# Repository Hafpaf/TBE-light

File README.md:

# TBE light
These are the source files for TBE lights shown at MCH2022. Original wiki page can be found here: [wiki.mch2022.org](https://wiki.mch2022.org/TBE_light)

## Credits
This project was funded by the [IFCAT foundation](https://ifcat.org/) for the technology festival [MCH2022](https://mch2022.org/).

Main contributors where:
- [Hafnium](https://github.com/hafpaf/): holding everything together
- [Oliver Taubenheim](https://www.facebook.com/a2kOliverTbm): CAD modelling
- [Richard Graham](https://github.com/Richard42Graham): PCB design

A big thanks to all contributors that helped during the prototyping of this project.

## Details

The LED controller uses an ESP32 with an LAN8720A chip for Ethernet connection and is compatible with [WLED](https://github.com/Aircoookie/WLED).

The repository is split into two categories
- [PCB](./PCB/): contains Gerber files for LED controller board, as well as an component list.
-  [CAD](./CAD/): contains to Adobe Illustrator files that can be opened in [Lightburn](https://lightburnsoftware.com/) or similar laser cutting software.

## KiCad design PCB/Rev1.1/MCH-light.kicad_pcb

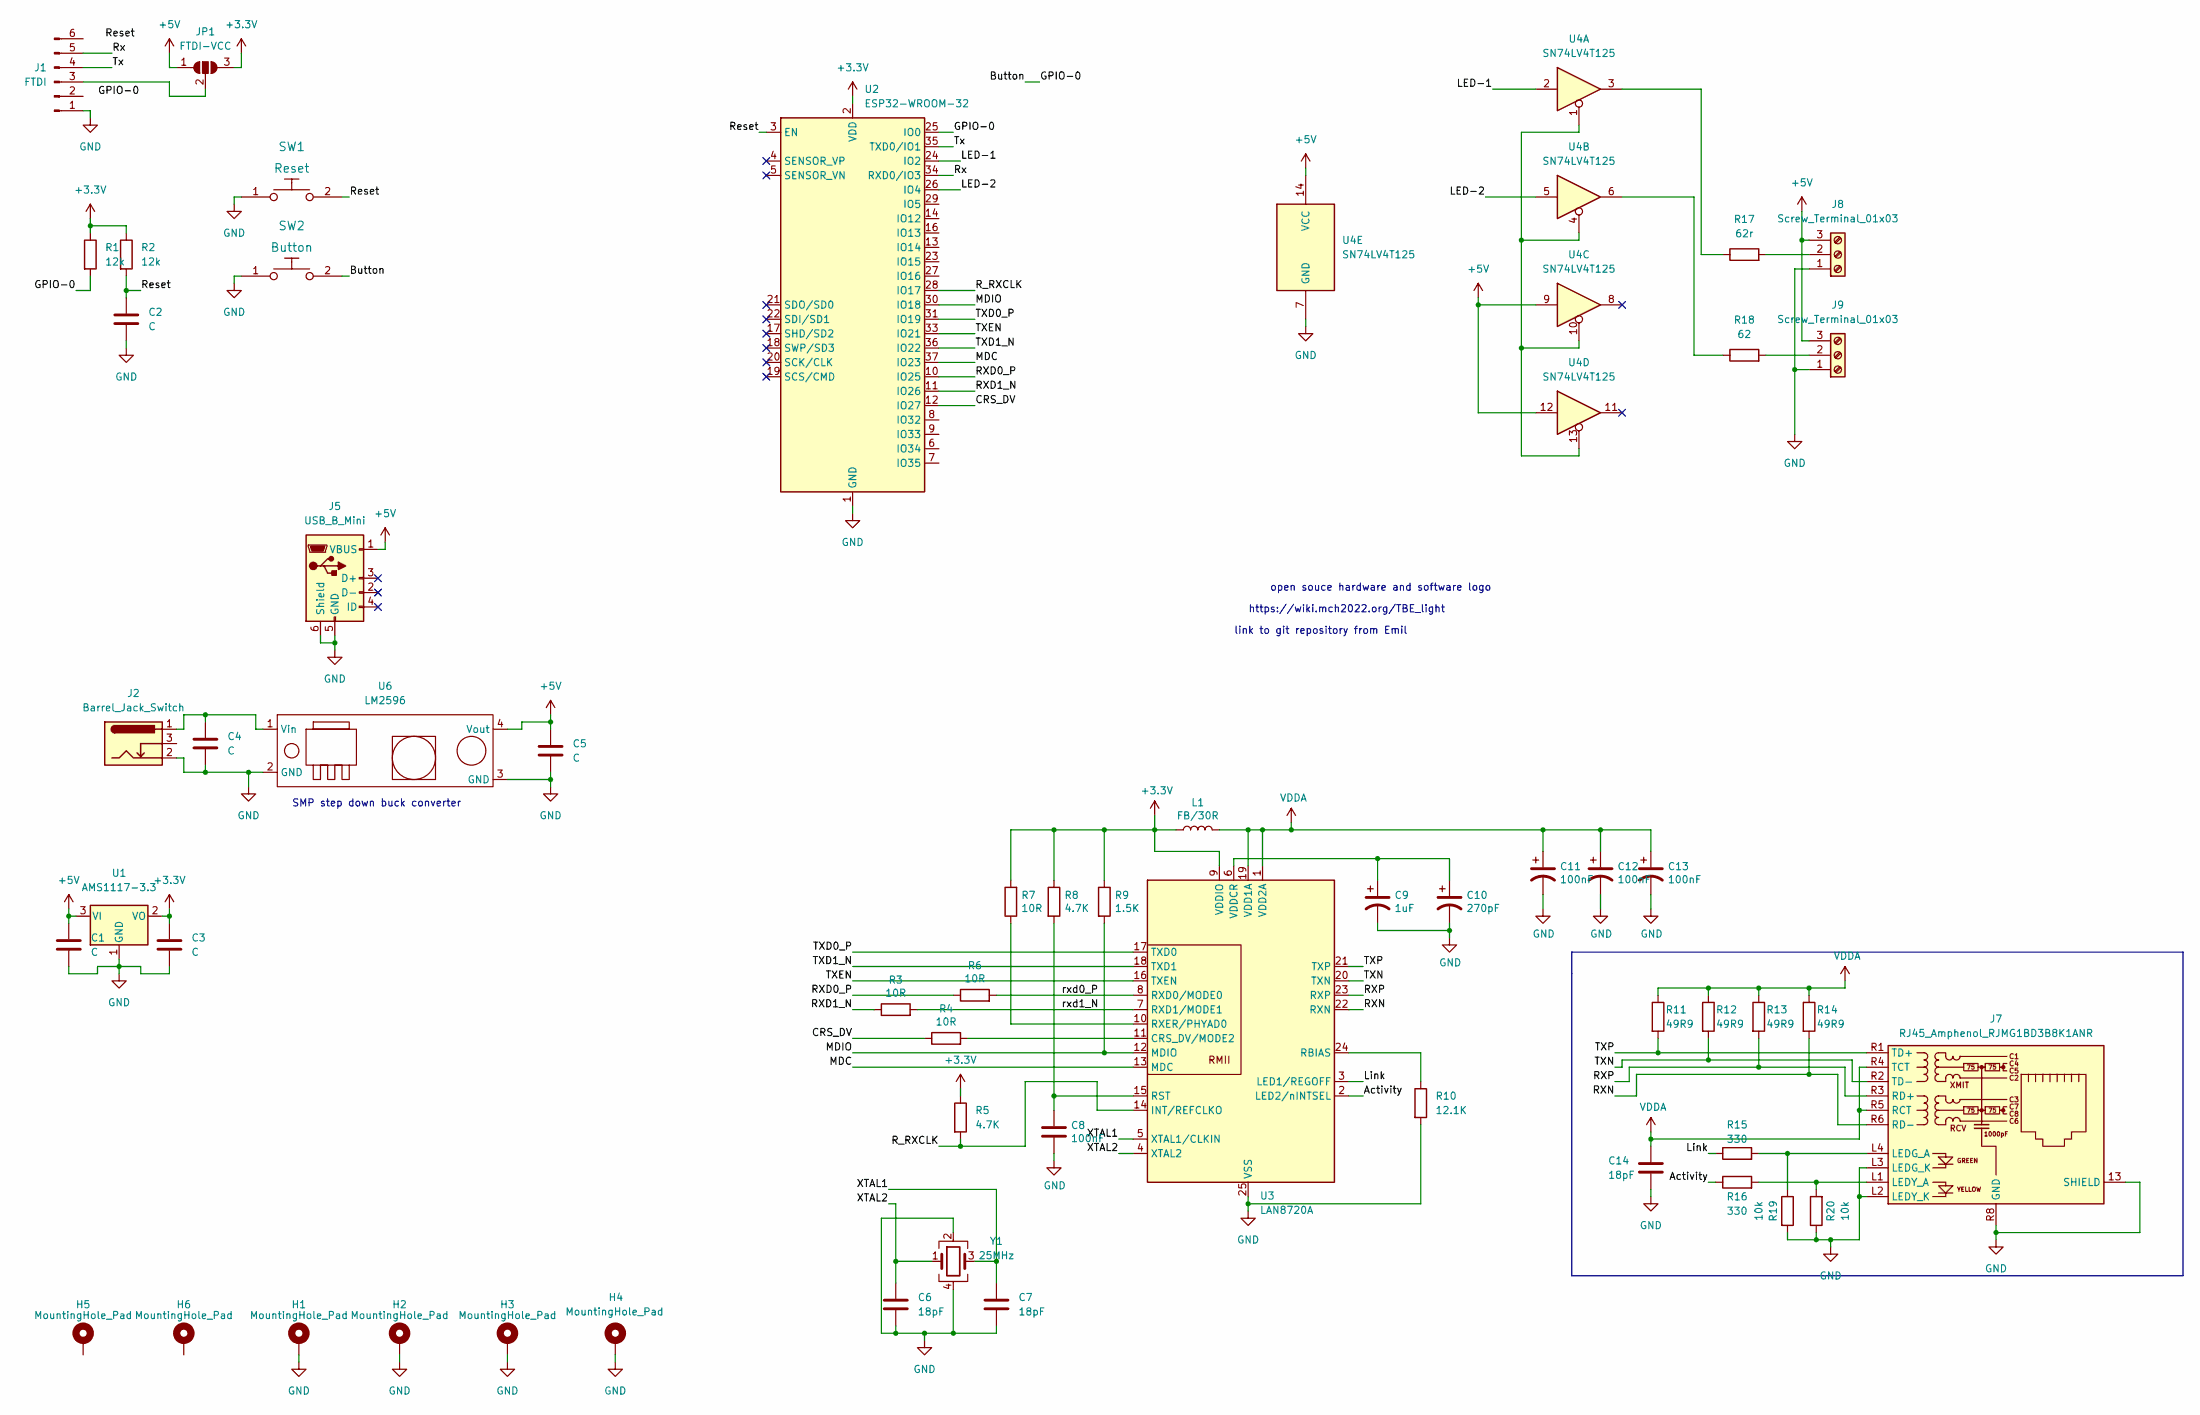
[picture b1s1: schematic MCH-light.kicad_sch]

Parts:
C1, C2, C3, C4, C5: C; C_0805_2012Metric
C6, C7, C14: 18pF; C_0805_2012Metric
C8, C11, C12, C13: 100nF; C_0603_1608Metric
C9: 1uF; C_0603_1608Metric
C10: 270pF; C_0603_1608Metric
H1, H2, H3, H4, H5, H6: MountingHole_Pad; MountingHole_3.2mm_M3_Pad
J1: FTDI; PinSocket_1x06_P2.54mm_Vertical
J2: Barrel_Jack_Switch; BarrelJack_GCT_DCJ200-10-A_Horizontal
J5: USB_B_Mini; USB_Micro-AB_Molex_47590-0001; JLC-pcb-part C136001
J7: RJ45_Amphenol_RJMG1BD3B8K1ANR; JLC-pcb-part C456388
J8, J9: Screw_Terminal_01x03; PinSocket_1x03_P2.54mm_Vertical
JP1: FTDI-VCC; SolderJumper-3_P1.3mm_Open_RoundedPad1.0x1.5mm
L1: FB/30R; L_0805_2012Metric
R1, R2: 12k; R_0603_1608Metric
R3, R4, R6, R7: 10R; R_0603_1608Metric
R5: 4.7K; C_0805_2012Metric
R8: 4.7K; R_0603_1608Metric
R9: 1.5K; R_0603_1608Metric
R10: 12.1K; R_0603_1608Metric
R11, R12, R13, R14: 49R9; R_0603_1608Metric
R15, R16: 330; R_0603_1608Metric
R17: 62r; R_0603_1608Metric
R18: 62; R_0603_1608Metric
R19, R20: 10k; R_0603_1608Metric
SW1: Reset; SW_PUSH_6mm; JLC-pcb-part C13828
SW2: Button; SW_PUSH_6mm; JLC-pcb-part C13828
U1: AMS1117-3.3; SOT-223-3_TabPin2; JLC-pcb-part C173386
U2: ESP32-WROOM-32; JLC-pcb-part C473012
U3: LAN8720A; QFN-24-1EP_4x4mm_P0.5mm_EP2.6x2.6mm; JLC-pcb-part C45223
U4: SN74LV4T125; TSSOP-14_4.4x5mm_P0.65mm; JLC-pcb-part C90755
U6: LM2596; LM2596-Module
Y1: 25MHz; Crystal_SMD_Abracon_ABM8G-4Pin_3.2x2.5mm

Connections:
+3V3: C3.1, JP1.3 (B), L1.1, R1.1, R2.1, R5.1, R7.2, R8.1, R9.1, U1.2 (VO), U2.2 (VDD), U3.9 (VDDIO)
+5V: C1.1, C5.1, J5.1 (VBUS), J8.3, J9.3, JP1.1 (A), U1.3 (VI), U4.9, U4.12, U4.14 (VCC), U6.4 (Vout)
/Activity: R16.1, U3.2 (LED2/nINTSEL)
/Button: R1.2, SW2.2, U2.25 (IO0)
/CRS_DV: R4.1, U2.12 (IO27)
/LED-1: U2.24 (IO2), U4.2
/LED-2: U2.26 (IO4), U4.5
/Link: R15.1, U3.3 (LED1/REGOFF)
/MDC: U2.37 (IO23), U3.13 (MDC)
/MDIO: R9.2, U2.30 (IO18), U3.12 (MDIO)
/RXD0_P: R6.1, U2.10 (IO25)
/RXD1_N: R3.1, U2.11 (IO26)
/RXN: J7.R6 (RD-), R14.2, U3.22 (RXN)
/RXP: J7.R3 (RD+), R13.2, U3.23 (RXP)
/R_RXCLK: R5.2, U2.28 (IO17), U3.14 (INT/REFCLKO)
/Reset: C2.1, R2.2, SW1.2, U2.3 (EN)
/Rx: J1.5, U2.34 (RXD0/IO3)
/TXD0_P: U2.31 (IO19), U3.17 (TXD0)
/TXD1_N: U2.36 (IO22), U3.18 (TXD1)
/TXEN: U2.33 (IO21), U3.16 (TXEN)
/TXN: J7.R2 (TD-), R12.2, U3.20 (TXN)
/TXP: J7.R1 (TD+), R11.2, U3.21 (TXP)
/Tx: J1.4, U2.35 (TXD0/IO1)
/XTAL1: C7.1, U3.5 (XTAL1/CLKIN), Y1.3
/XTAL2: C6.1, U3.4 (XTAL2), Y1.1
/rxd0_P: R6.2, U3.8 (RXD0/MODE0)
/rxd1_N: R3.2, U3.7 (RXD1/MODE1)
GND: C1.2, C2.2, C3.2, C4.2, C5.2, C6.2, C7.2, C8.2, C9.2, C10.2, C11.2, C12.2, C13.2, C14.2, H1.1, H2.1, H3.1, H4.1, J1.1, J2.2, J5.5 (GND), J5.6 (Shield), J7.13 (SHIELD), J7.L2 (LEDY_K), J7.L3 (LEDG_K), J7.R8 (GND), J8.1, J9.1, R10.2, R19.2, R20.1, SW1.1, SW2.1, U1.1 (GND), U2.1 (GND), U2.15 (GND), U2.38 (GND), U2.39 (GND), U3.25 (VSS), U4.7 (GND), U6.2 (GND), U6.3 (GND), Y1.2, Y1.4
unnamed: C4.1, J2.1, U6.1 (Vin)
unnamed: C8.1, R8.2, U3.15 (RST)
unnamed: C9.1, C10.1, U3.6 (VDDCR)
unnamed: J1.3, JP1.2 (C)
unnamed: J7.L1 (LEDY_A), R16.2, R20.2
unnamed: J7.L4 (LEDG_A), R15.2, R19.1
unnamed: J8.2, R17.2
unnamed: J9.2, R18.2
unnamed: R4.2, U3.11 (CRS_DV/MODE2)
unnamed: R7.1, U3.10 (RXER/PHYAD0)
unnamed: R10.1, U3.24 (RBIAS)
unnamed: R17.1, U4.3
unnamed: R18.1, U4.6
unnamed: U4.1, U4.4, U4.10, U4.13
VDDA: C11.1, C12.1, C13.1, C14.1, J7.R4 (TCT), J7.R5 (RCT), L1.2, R11.1, R12.1, R13.1, R14.1, U3.1 (VDD2A), U3.19 (VDD1A)

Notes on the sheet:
https://wiki.mch2022.org/TBE_light
open souce hardware and software logo
link to git repository from Emil
SMP step down buck converter

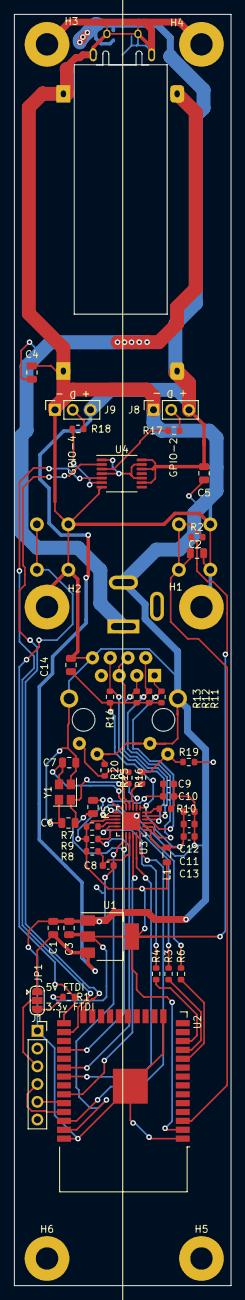
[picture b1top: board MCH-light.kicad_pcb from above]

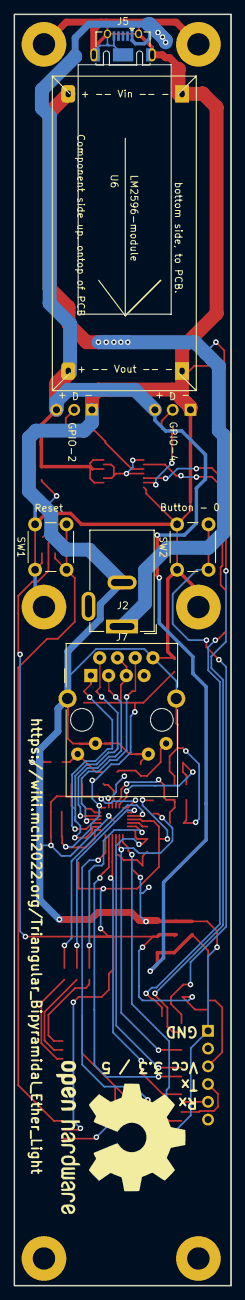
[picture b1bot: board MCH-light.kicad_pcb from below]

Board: 2 copper layers, 31.0 x 181.9 mm, 56 parts (6 on the bottom side), 43 nets.

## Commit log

2022-07-08 init
2022-07-10 add credits
2022-07-15 fixed some hardware bugs in the shcmatic, but have not finished the fixed layout :3
2022-07-20 routed updated pcb, added some more silk screen labling, :3
2023-12-09 Readme: add image of final product
2023-12-09 readme: decrease image height
